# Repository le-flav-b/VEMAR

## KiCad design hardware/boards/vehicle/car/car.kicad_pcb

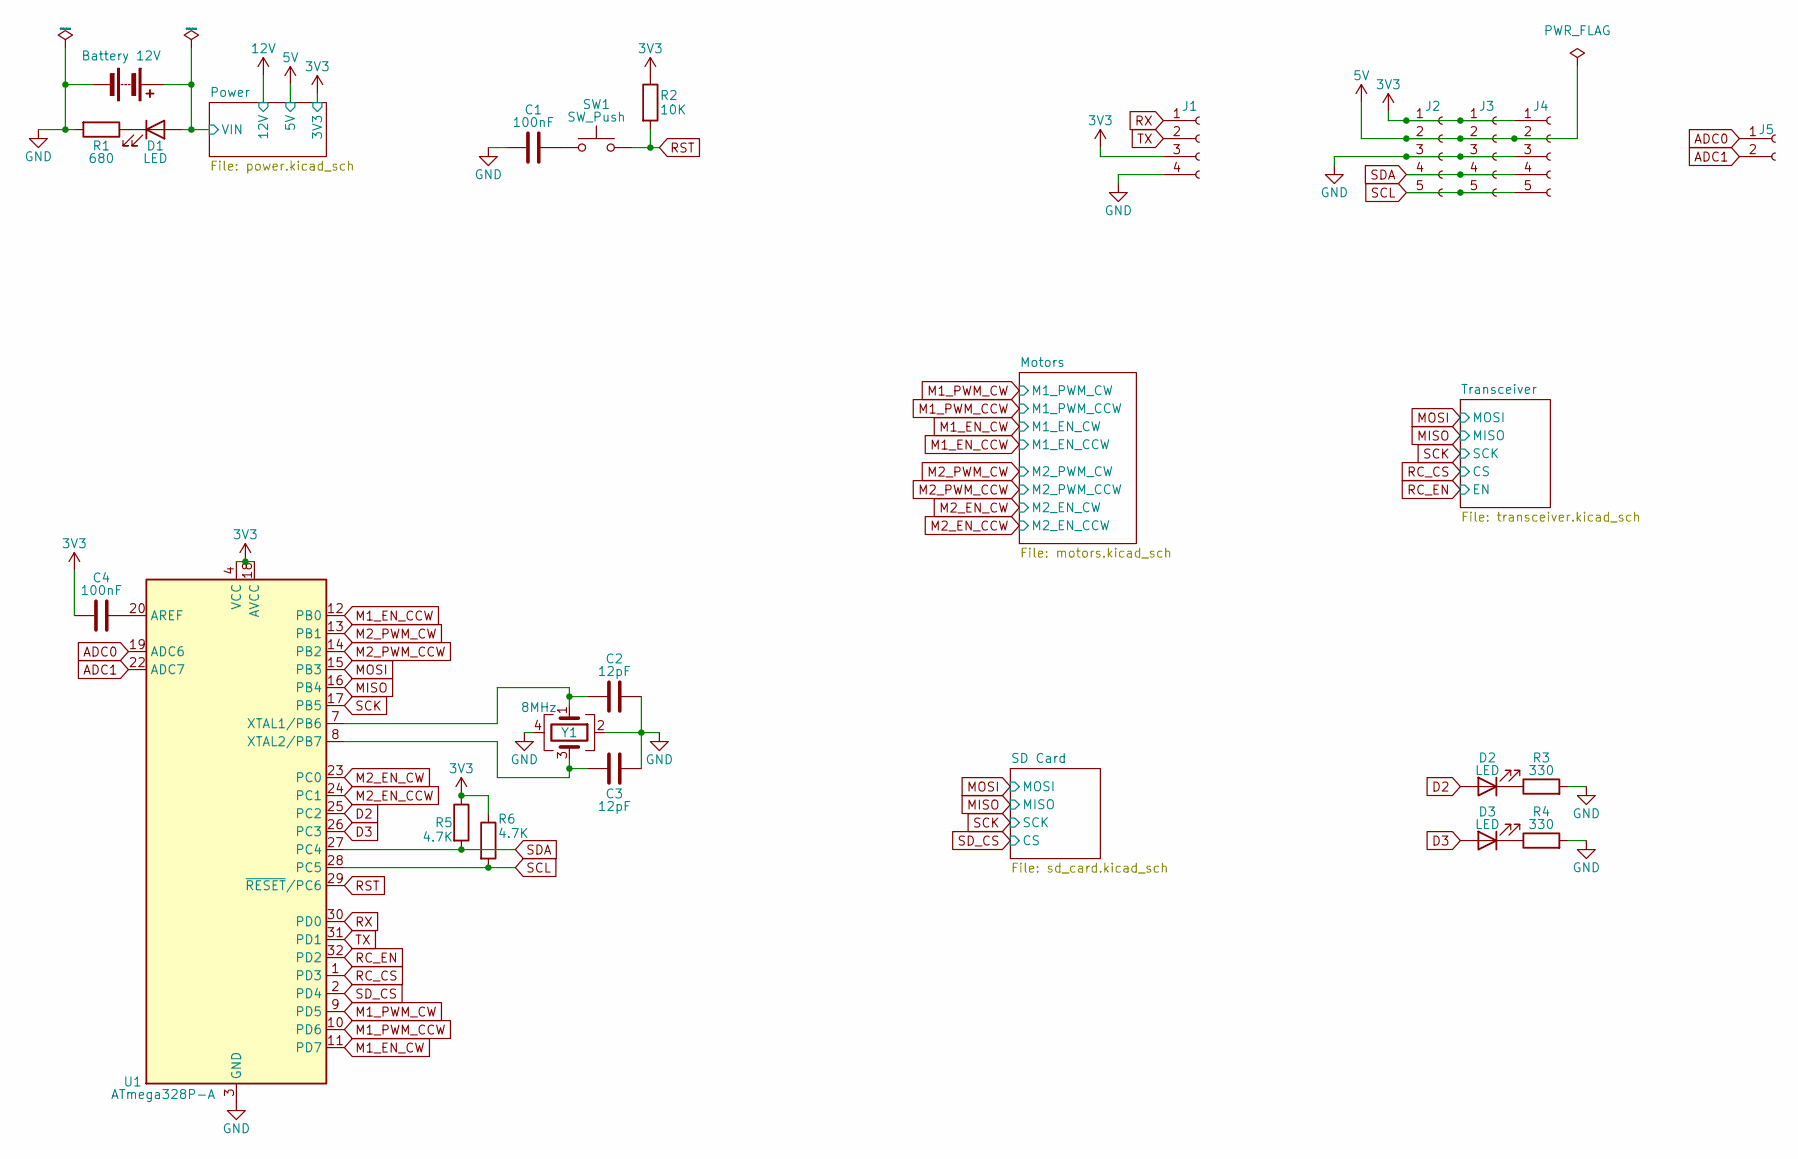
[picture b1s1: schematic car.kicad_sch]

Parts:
BT1: Battery 12V; PinHeader_1x02_P2.54mm_Vertical
C1, C4: 100nF; C_0603_1608Metric_Pad1.08x0.95mm_HandSolder
C2, C3: 12pF; C_0603_1608Metric_Pad1.08x0.95mm_HandSolder
D1, D2, D3: LED; LED_0603_1608Metric_Pad1.05x0.95mm_HandSolder
J1: Conn_01x04_Socket; PinHeader_1x04_P2.54mm_Vertical
J2, J3, J4: Conn_01x05_Socket; PinHeader_1x05_P2.54mm_Vertical
J5: Conn_01x02_Socket; PinHeader_1x02_P2.54mm_Vertical
R1: 680; R_0603_1608Metric_Pad0.98x0.95mm_HandSolder
R2: 10K; R_0603_1608Metric_Pad0.98x0.95mm_HandSolder
R3, R4: 330; R_0603_1608Metric_Pad0.98x0.95mm_HandSolder
R5, R6: 4.7K; R_0603_1608Metric_Pad0.98x0.95mm_HandSolder
SW1: SW_Push; SW_Tactile3x2.5
U1: ATmega328P-A; TQFP-32_7x7mm_P0.8mm
Y1: 8MHz; crys_osc_smd3225_4

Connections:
3V3: C4.1, J1.3, J2.1, J3.1, J4.1, R2.1, R5.1, R6.1, U1.4 (VCC), U1.6 (VCC), U1.18 (AVCC); also elsewhere on the board
5V: J2.2, J3.2, J4.2; also elsewhere on the board
12V: BT1.1 (+), D1.2 (A); also elsewhere on the board
ADC0: J5.1, U1.19 (ADC6)
ADC1: J5.2, U1.22 (ADC7)
D2: D2.2 (A), U1.25 (PC2)
D3: D3.2 (A), U1.26 (PC3)
GND: BT1.2 (-), C1.1, C2.2, C3.2, J1.4, J2.3, J3.3, J4.3, R1.2, R3.2, R4.2, U1.3 (GND), U1.5 (GND), U1.21 (GND), Y1.2, Y1.4; also elsewhere on the board
M1_EN_CCW: U1.12 (PB0); also elsewhere on the board
M1_EN_CW: U1.11 (PD7); also elsewhere on the board
M1_PWM_CCW: U1.10 (PD6); also elsewhere on the board
M1_PWM_CW: U1.9 (PD5); also elsewhere on the board
M2_EN_CCW: U1.24 (PC1); also elsewhere on the board
M2_EN_CW: U1.23 (PC0); also elsewhere on the board
M2_PWM_CCW: U1.14 (PB2); also elsewhere on the board
M2_PWM_CW: U1.13 (PB1); also elsewhere on the board
MISO: U1.16 (PB4); also elsewhere on the board
MOSI: U1.15 (PB3); also elsewhere on the board
unnamed: C1.2, SW1.1
unnamed: D1.1 (K), R1.1
unnamed: D2.1 (K), R3.1
unnamed: D3.1 (K), R4.1
unnamed: C4.2, U1.20 (AREF)
unnamed: C2.1, U1.7 (XTAL1/PB6), Y1.1
unnamed: C3.1, U1.8 (XTAL2/PB7), Y1.3
RC_CS: U1.1 (PD3); also elsewhere on the board
RC_EN: U1.32 (PD2); also elsewhere on the board
RST: R2.2, SW1.2, U1.29 (~RESET/PC6)
RX: J1.1, U1.30 (PD0)
SCK: U1.17 (PB5); also elsewhere on the board
SCL: J2.5, J3.5, J4.5, R6.2, U1.28 (PC5)
SDA: J2.4, J3.4, J4.4, R5.2, U1.27 (PC4)
SD_CS: U1.2 (PD4); also elsewhere on the board
TX: J1.2, U1.31 (PD1)

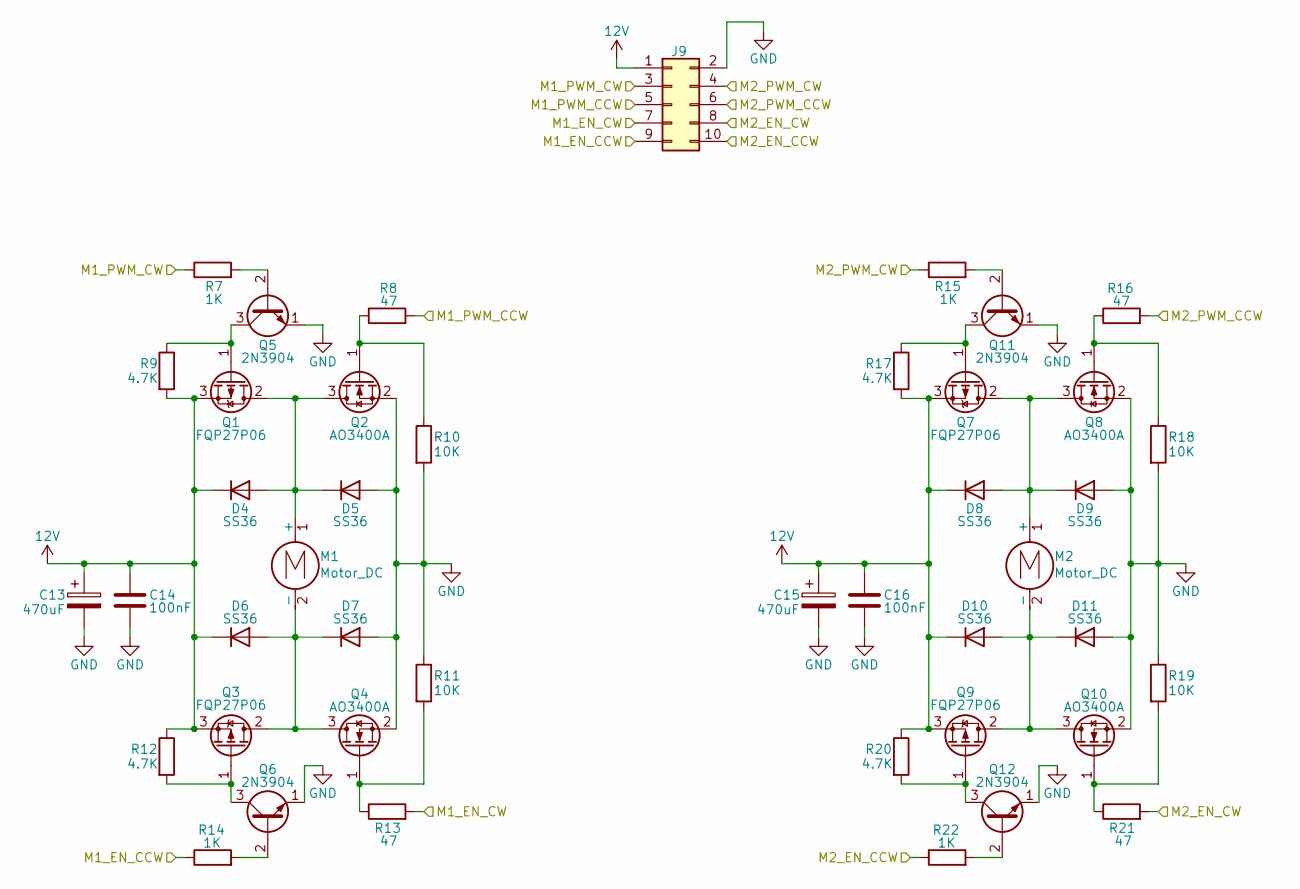
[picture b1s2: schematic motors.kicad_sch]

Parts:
C13, C15: 470uF; CP_Radial_D10.0mm_P5.00mm
C14, C16: 100nF; C_0603_1608Metric_Pad1.08x0.95mm_HandSolder
D4, D5, D6, D7, D8, D9, D10, D11: SS36; D_SMA_Handsoldering
J9: Conn_02x05_Odd_Even; PinHeader_2x05_P2.54mm_Vertical
M1, M2: Motor_DC; PinHeader_1x02_P2.54mm_Vertical
Q1, Q3, Q7, Q9: FQP27P06; TO-220-3_Vertical
Q2, Q4, Q8, Q10: AO3400A; SOT-23
Q5, Q6, Q11, Q12: 2N3904; TO-92_Inline
R7, R14, R15, R22: 1K; R_0603_1608Metric_Pad0.98x0.95mm_HandSolder
R8, R13, R16, R21: 47; R_0603_1608Metric_Pad0.98x0.95mm_HandSolder
R9, R12, R17, R20: 4.7K; R_0603_1608Metric_Pad0.98x0.95mm_HandSolder
R10, R11, R18, R19: 10K; R_0603_1608Metric_Pad0.98x0.95mm_HandSolder

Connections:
12V: C13.1, C14.1, C15.1, C16.1, D4.1 (K), D6.1 (K), D8.1 (K), D10.1 (K), J9.1, Q1.3 (S), Q3.3 (S), Q7.3 (S), Q9.3 (S), R9.2, R12.1, R17.2, R20.1; also elsewhere on the board
GND: C13.2, C14.2, C15.2, C16.2, D5.2 (A), D7.2 (A), D9.2 (A), D11.2 (A), J9.2, Q2.2 (S), Q4.2 (S), Q5.1 (E), Q6.1 (E), Q8.2 (S), Q10.2 (S), Q11.1 (E), Q12.1 (E), R10.2, R11.1, R18.2, R19.1; also elsewhere on the board
M1_EN_CCW: J9.9, R14.1; also elsewhere on the board
M1_EN_CW: J9.7, R13.2; also elsewhere on the board
M1_PWM_CCW: J9.5, R8.2; also elsewhere on the board
M1_PWM_CW: J9.3, R7.1; also elsewhere on the board
M2_EN_CCW: J9.10, R22.1; also elsewhere on the board
M2_EN_CW: J9.8, R21.2; also elsewhere on the board
M2_PWM_CCW: J9.6, R16.2; also elsewhere on the board
M2_PWM_CW: J9.4, R15.1; also elsewhere on the board
unnamed: D4.2 (A), D5.1 (K), M1.1 (+), Q1.2 (D), Q2.3 (D)
unnamed: D6.2 (A), D7.1 (K), M1.2 (-), Q3.2 (D), Q4.3 (D)
unnamed: D8.2 (A), D9.1 (K), M2.1 (+), Q7.2 (D), Q8.3 (D)
unnamed: D10.2 (A), D11.1 (K), M2.2 (-), Q9.2 (D), Q10.3 (D)
unnamed: Q1.1 (G), Q5.3 (C), R9.1
unnamed: Q2.1 (G), R8.1, R10.1
unnamed: Q3.1 (G), Q6.3 (C), R12.2
unnamed: Q4.1 (G), R11.2, R13.1
unnamed: Q5.2 (B), R7.2
unnamed: Q6.2 (B), R14.2
unnamed: Q8.1 (G), R16.1, R18.1
unnamed: Q10.1 (G), R19.2, R21.1
unnamed: Q11.2 (B), R15.2
unnamed: Q7.1 (G), Q11.3 (C), R17.1
unnamed: Q12.2 (B), R22.2
unnamed: Q9.1 (G), Q12.3 (C), R20.2

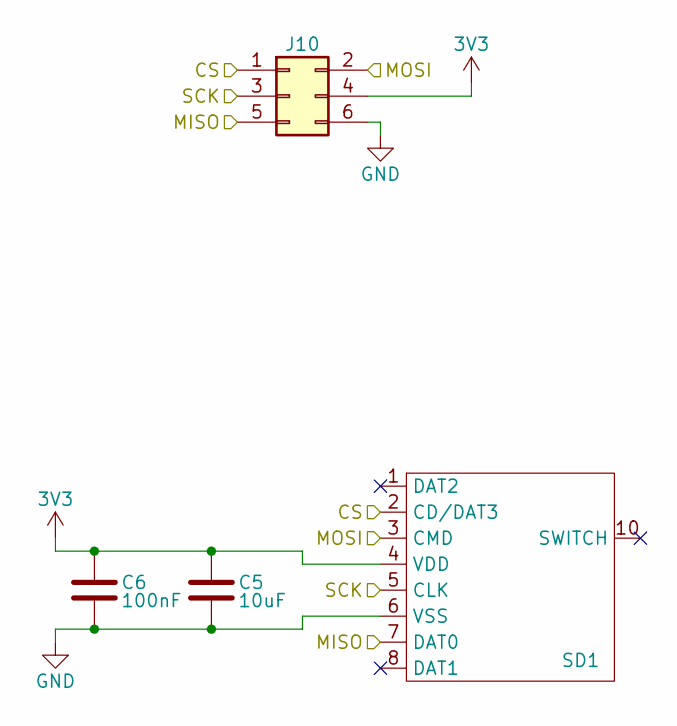
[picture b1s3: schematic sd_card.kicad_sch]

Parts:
C5: 10uF; C_0603_1608Metric_Pad1.08x0.95mm_HandSolder
C6: 100nF; C_0603_1608Metric_Pad1.08x0.95mm_HandSolder
J10: Conn_02x03_Odd_Even; PinHeader_2x03_P2.54mm_Vertical
SD1: SD_SLOT

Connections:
3V3: C5.1, C6.1, J10.4, SD1.4 (VDD); also elsewhere on the board
GND: C5.2, C6.2, J10.6, SD1.6 (VSS); also elsewhere on the board
MISO: J10.5, SD1.7 (DAT0); also elsewhere on the board
MOSI: J10.2, SD1.3 (CMD); also elsewhere on the board
SCK: J10.3, SD1.5 (CLK); also elsewhere on the board
SD_CS: J10.1, SD1.2 (CD/DAT3); also elsewhere on the board

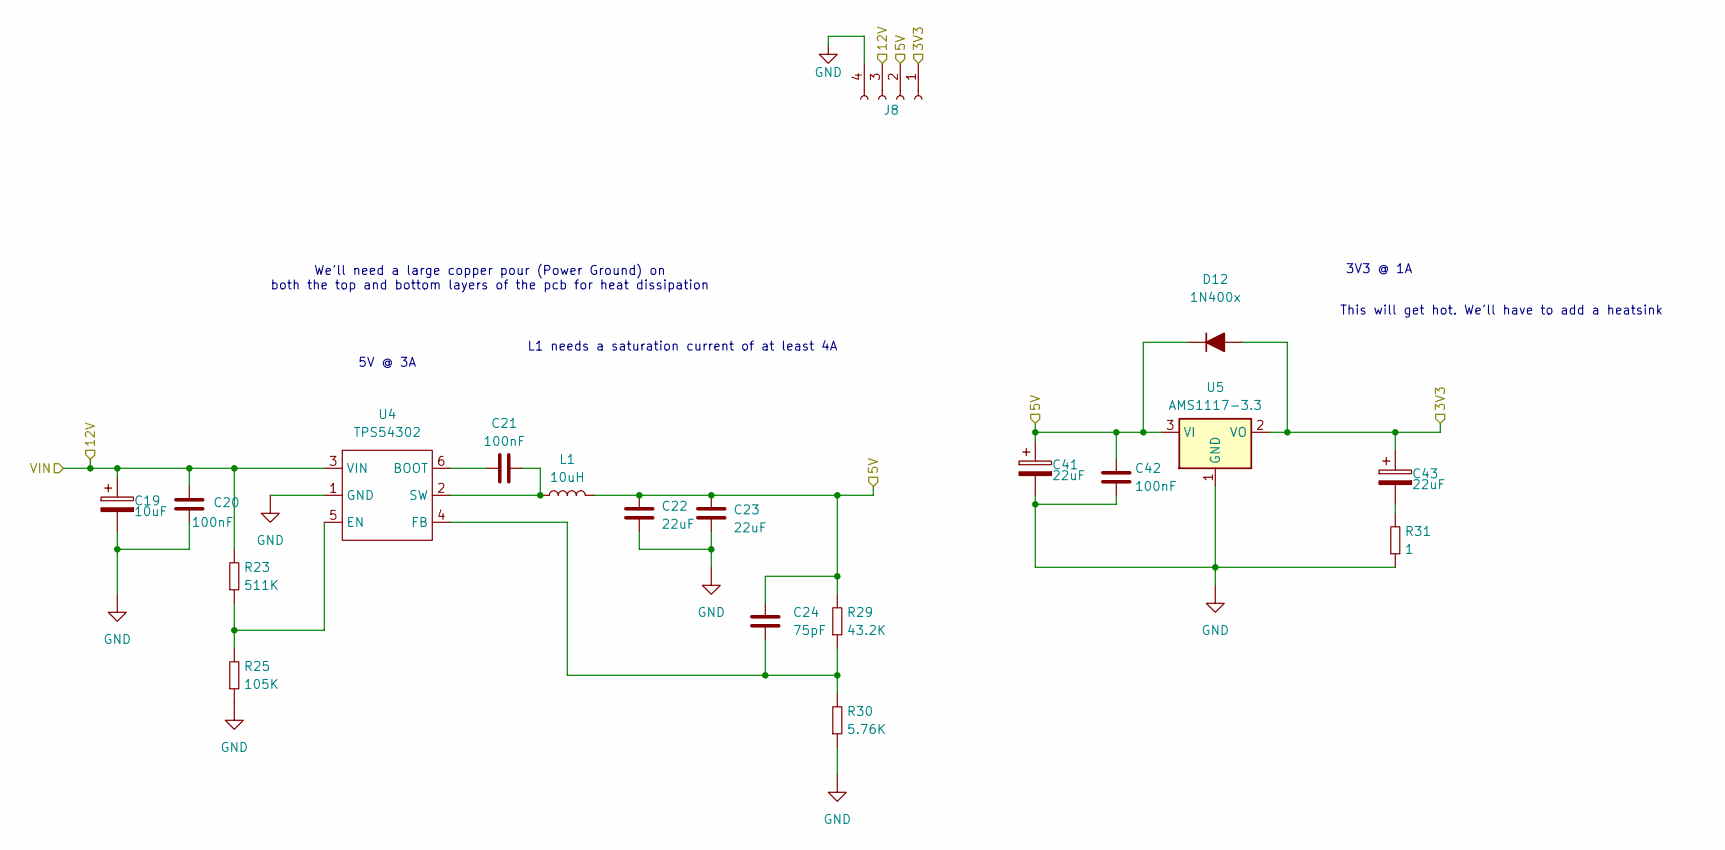
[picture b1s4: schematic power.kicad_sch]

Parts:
C19: 10uF; CP_Radial_D5.0mm_P2.00mm
C20, C21, C42: 100nF; C_0603_1608Metric_Pad1.08x0.95mm_HandSolder
C22, C23: 22uF; C_0603_1608Metric_Pad1.08x0.95mm_HandSolder
C24: 75pF; C_0603_1608Metric_Pad1.08x0.95mm_HandSolder
C41, C43: 22uF; CP_Radial_D5.0mm_P2.00mm
D12: 1N400x; D_DO-41_SOD81_P2.54mm_Vertical_AnodeUp
J8: Conn_01x04_Socket; PinHeader_1x04_P2.54mm_Vertical
L1: 10uH; L_0603_1608Metric_Pad1.05x0.95mm_HandSolder
R23: 511K; R_0603_1608Metric_Pad0.98x0.95mm_HandSolder
R25: 105K; R_0603_1608Metric_Pad0.98x0.95mm_HandSolder
R29: 43.2K; R_0603_1608Metric_Pad0.98x0.95mm_HandSolder
R30: 5.76K; R_0603_1608Metric_Pad0.98x0.95mm_HandSolder
R31: 1; R_0603_1608Metric_Pad0.98x0.95mm_HandSolder
U4: TPS54302; TSOT-23-6_HandSoldering
U5: AMS1117-3.3; SOT-223-3_TabPin2

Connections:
3V3: C43.1, D12.2 (A), J8.1, U5.2 (VO); also elsewhere on the board
5V: C22.1, C23.2, C24.2, C41.1, C42.2, D12.1 (K), J8.2, L1.2, R29.2, U5.3 (VI); also elsewhere on the board
12V: C19.1, C20.2, J8.3, R23.2, U4.3 (VIN); also elsewhere on the board
GND: C19.2, C20.1, C22.2, C23.1, C41.2, C42.1, J8.4, R25.1, R30.1, R31.1, U4.1 (GND), U5.1 (GND); also elsewhere on the board
unnamed: C43.2, R31.2
unnamed: C21.1, U4.6 (BOOT)
unnamed: R23.1, R25.2, U4.5 (EN)
unnamed: C24.1, R29.1, R30.2, U4.4 (FB)
unnamed: C21.2, L1.1, U4.2 (SW)

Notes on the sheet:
We'll need a large copper pour (Power Ground) on both the top and bottom layers of the pcb for heat dissipation
5V @ 3A
L1 needs a saturation current of at least 4A
This will get hot. We'll have to add a heatsink
3V3 @ 1A

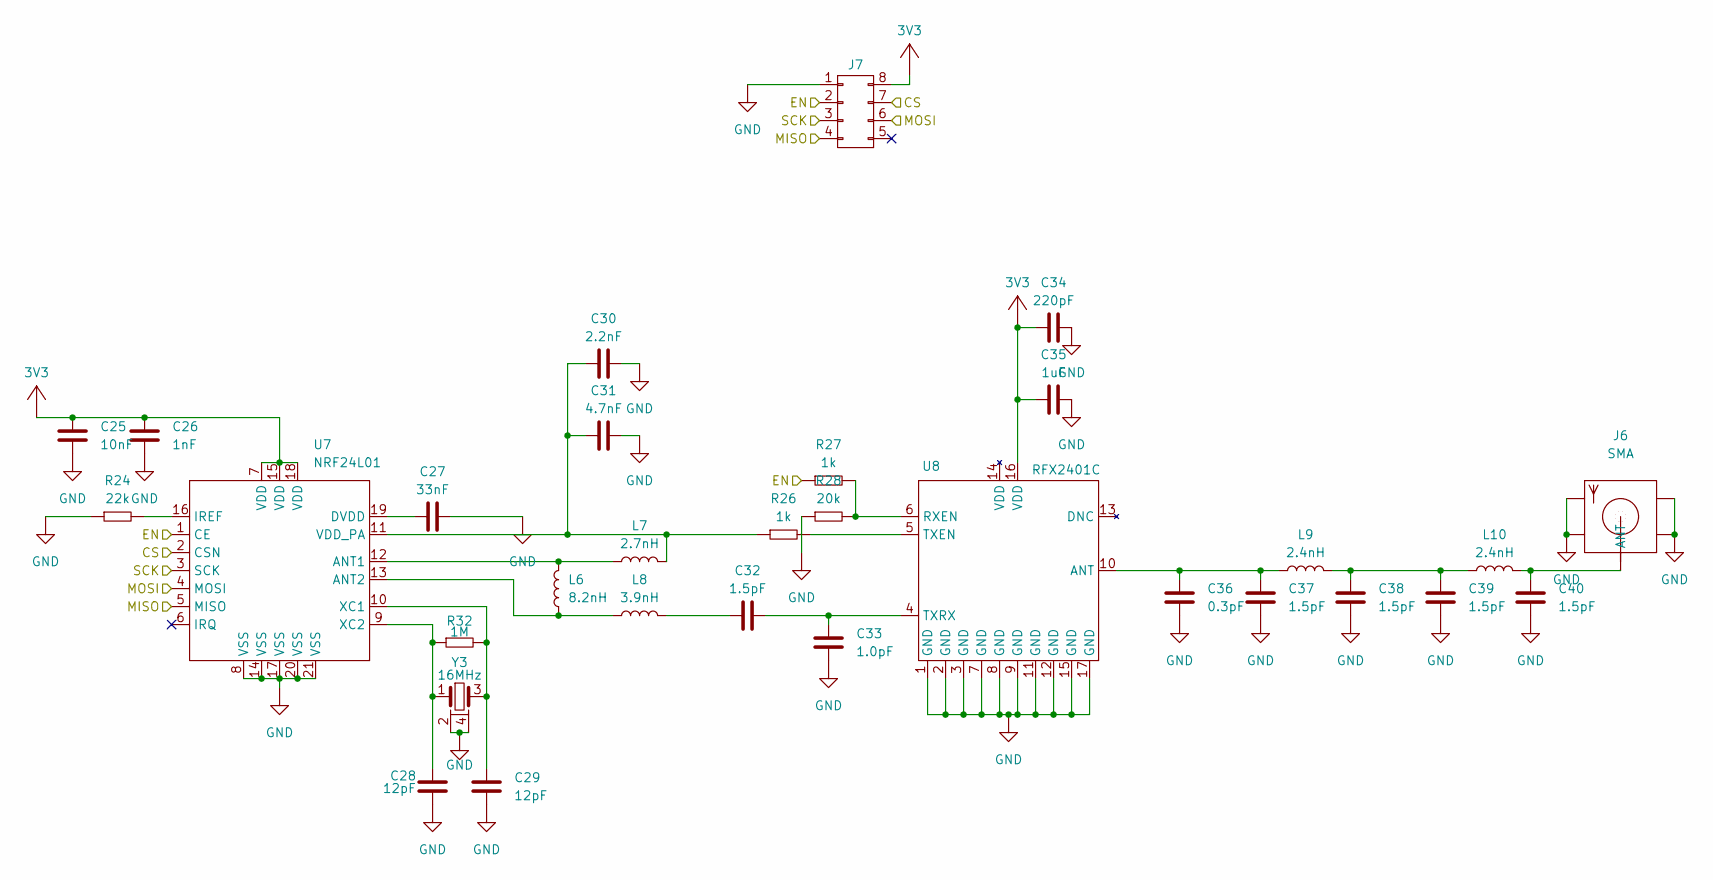
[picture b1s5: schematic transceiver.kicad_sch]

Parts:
C25: 10nF; C_0603
C26: 1nF; C_0603
C27: 33nF; C_0603
C28, C29: 12pF; C_0603
C30: 2.2nF; C_0603
C31: 4.7nF; C_0603
C32, C37, C38, C39, C40: 1.5pF; C_0603
C33: 1.0pF; C_0603
C34: 220pF; C_0603
C35: 1uF; C_0603
C36: 0.3pF; C_0603
J6: SMA
J7: 02x04; Pin_02x04
L6: 8.2nH; L_0603
L7: 2.7nH; L_0603
L8: 3.9nH; L_0603
L9, L10: 2.4nH; L_0603
R24: 22k; R_0603
R26, R27: 1k; R_0603
R28: 20k; R_0603
R32: 1M; R_0603
U7: NRF24L01; NRF24L01_QFN20
U8: RFX2401C; RFX2401C_QFN16
Y3: 16MHz; Crystal_3225

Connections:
3V3: C25.2, C26.2, C34.1, C35.1, J7.8, U7.7 (VDD), U7.15 (VDD), U7.18 (VDD), U8.16 (VDD); also elsewhere on the board
GND: C25.1, C26.1, C27.2, C28.1, C29.1, C30.2, C31.2, C33.1, C34.2, C35.2, C36.1, C37.1, C38.1, C39.1, C40.1, J6.2, J6.3, J6.4, J6.5, J7.1, R24.1, R28.1, U7.8 (VSS), U7.14 (VSS), U7.17 (VSS), U7.20 (VSS), U7.21 (VSS), U8.1 (GND), U8.2 (GND), U8.3 (GND), U8.7 (GND), U8.8 (GND), U8.9 (GND), U8.11 (GND), U8.12 (GND), U8.15 (GND), U8.17 (GND), Y3.2 (GND), Y3.4 (GND); also elsewhere on the board
MISO: J7.4, U7.5 (MISO); also elsewhere on the board
MOSI: J7.6, U7.4 (MOSI); also elsewhere on the board
unnamed: C32.1, L8.2
unnamed: C38.2, C39.2, L9.2, L10.1
unnamed: C40.2, J6.1 (ANT), L10.2
unnamed: L6.2, L7.1, U7.12 (ANT1)
unnamed: L6.1, L8.1, U7.13 (ANT2)
unnamed: C27.1, U7.19 (DVDD)
unnamed: R24.2, U7.16 (IREF)
unnamed: C30.1, C31.1, L7.2, R26.1, U7.11 (VDD_PA)
unnamed: C29.2, R32.2, U7.10 (XC1), Y3.3
unnamed: C28.2, R32.1, U7.9 (XC2), Y3.1
unnamed: C36.2, C37.2, L9.1, U8.10 (ANT)
unnamed: R27.2, R28.2, U8.6 (RXEN)
unnamed: R26.2, U8.5 (TXEN)
unnamed: C32.2, C33.2, U8.4 (TXRX)
RC_CS: J7.7, U7.2 (CSN); also elsewhere on the board
RC_EN: J7.2, R27.1, U7.1 (CE); also elsewhere on the board
SCK: J7.3, U7.3 (SCK); also elsewhere on the board

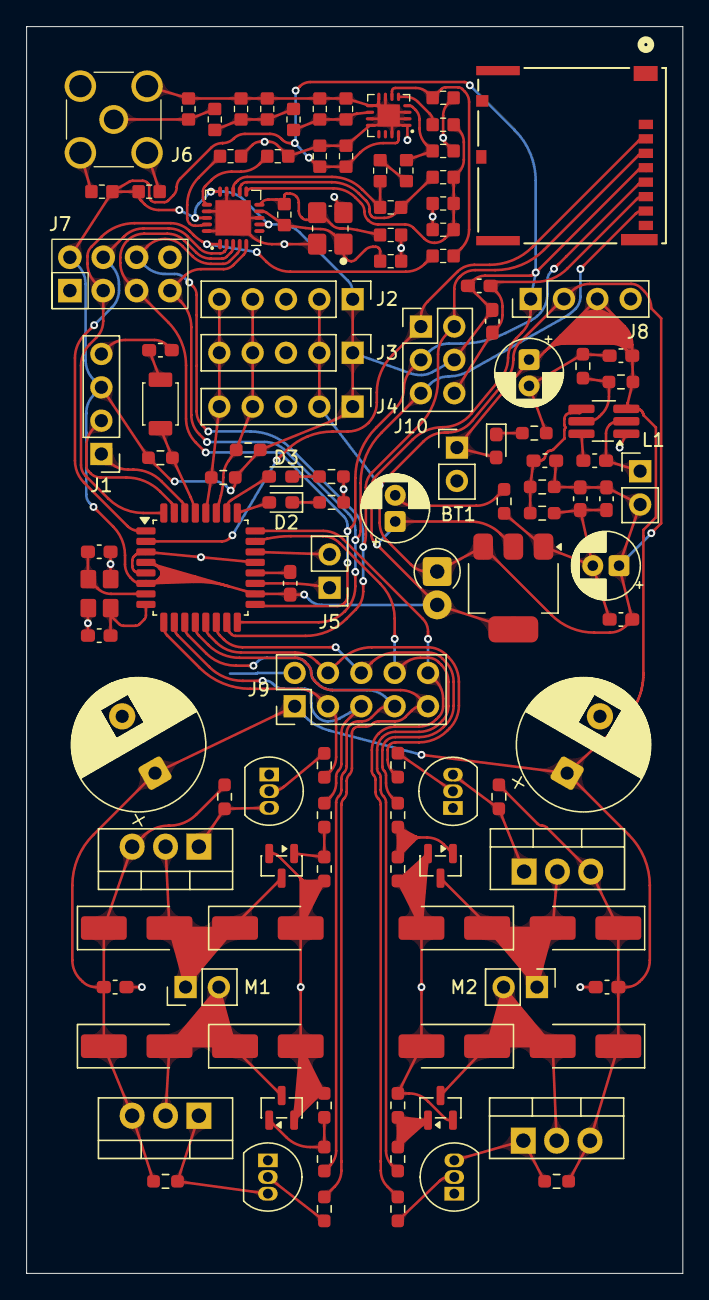
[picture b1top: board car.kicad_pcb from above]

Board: 2 copper layers, 50.0 x 95.0 mm, 119 parts (0 on the bottom side), 69 nets.

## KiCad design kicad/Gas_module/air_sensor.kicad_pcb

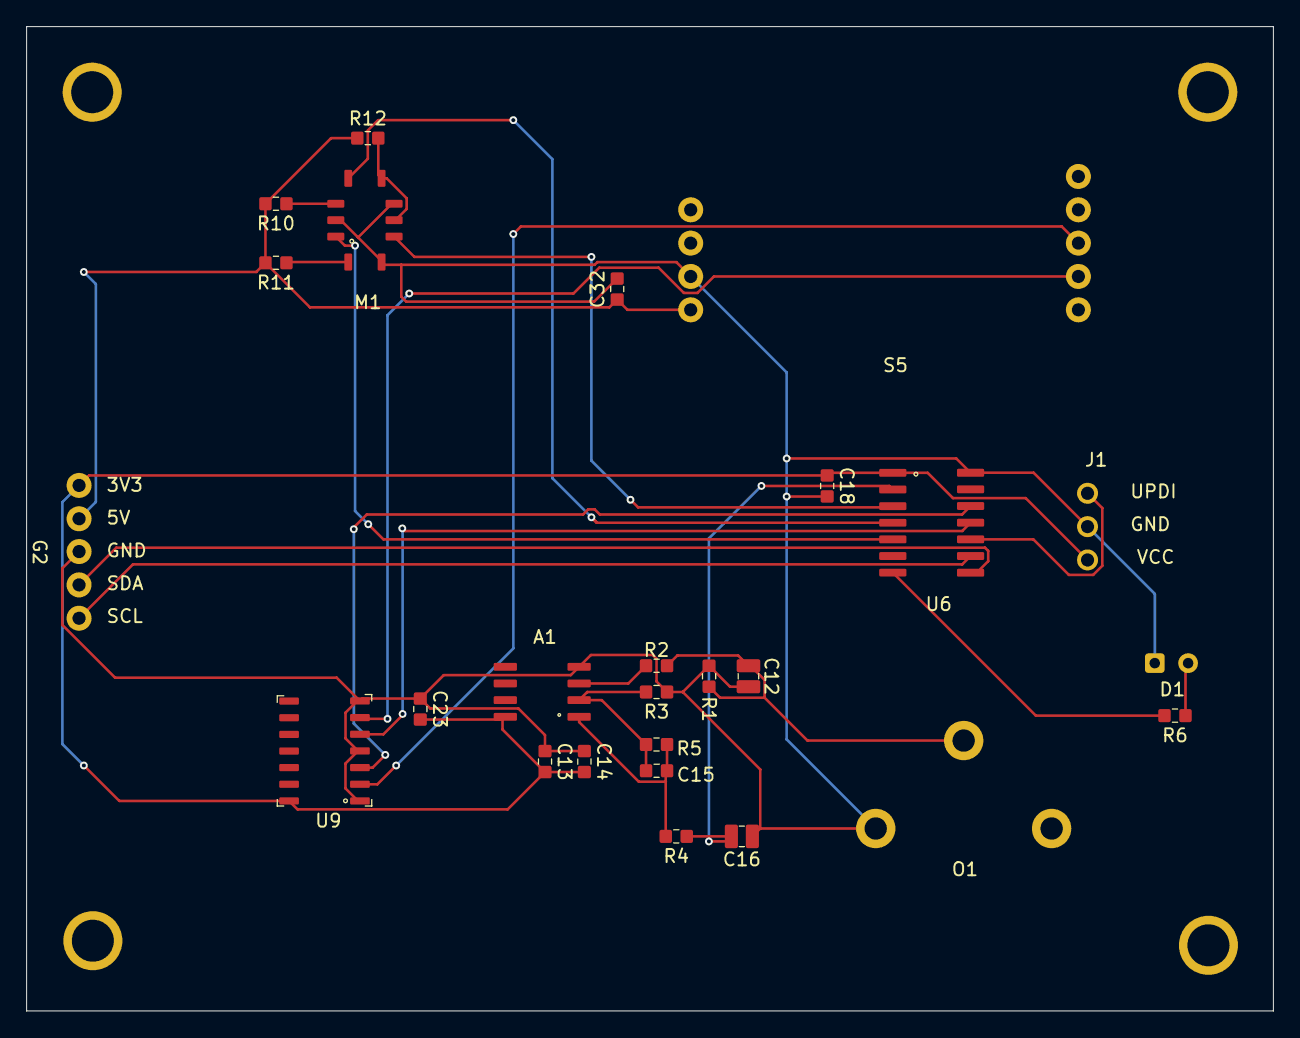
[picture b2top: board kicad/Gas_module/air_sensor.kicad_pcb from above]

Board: 2 copper layers, 95.0 x 75.0 mm, 26 parts (0 on the bottom side), 23 nets.

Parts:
A1: AD8552
C12: 4.7uF; C_0805
C13, C14, C15: 10nF; C_0603
C16: 10uF; C_0805
C18, C23, C32: 100nF; C_0603
D1: LED_3mm_THT
G2: Module Connector; GPIO_HEADER
J1: Program Header; ATtiny_Programming_Header
M1: MiCS-6814
O1: AO-03; AO_03
R1, R4: 100R; R_0603
R2, R3: 10K; R_0603
R5: 400K; R_0603
R6: 220; R_0603
R10: 27R; R_0603
R11: 130; R_0603
R12: 820R; R_0603
S5: MH-Z1911A
U6: ATtiny1614
U9: Buffer; SN74LVC125

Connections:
02_A: C16.2, R4.1, U6.2 (PA4)
3V3: A1.8 (+Vs), C13.2, C14.2, C18.1, C23.2, G2.1 (3V3), J1.1 (VCC), U6.1 (VDD), U9.14 (VCC)
5V: C32.1, G2.2 (5V), R10.2, R11.2, R12.1, S5.9 (VIN)
AT_GAS_RX: U6.12 (PA2), U9.3 (1Y)
AT_GAS_TX: U6.11 (PA1), U9.5 (2A)
C02_RX: S5.4 (RX), U9.6 (2Y)
CO2_TX: S5.3 (TX), U9.2 (1A)
CO_VAL: M1.8 (H), U6.3 (PA5)
GND: A1.4 (-Vs), C12.2, C13.1, C14.1, C16.1, C18.2, C23.1, C32.2, D1.1 (K), G2.3 (GND), J1.2 (GND), M1.2 (B), M1.6 (F), M1.9 (J), O1.2 (Vsensor-), R1.1, R3.1, S5.8 (GND), U6.14 (GND), U9.1 (1OE), U9.4 (2OE), U9.7 (GND)
NH3_VAL: M1.4 (D), U6.4 (PA6)
NO2_VAL: M1.1 (A), U6.5 (PA7)
unnamed: A1.3 (+IN_A), R2.2
unnamed: A1.2 (-IN_A), C15.2, R3.2, R5.2
unnamed: A1.1 (OUT_A), C15.1, R4.2, R5.1
unnamed: D1.2 (A), R6.2
unnamed: M1.3 (C), R10.1
unnamed: M1.5 (E), M1.7 (G), R12.2
unnamed: M1.10 (K), R11.1
unnamed: C12.1, O1.1 (Vsensor+), R1.2, R2.1
SCL: G2.5 (SCL), U6.9 (PB0)
SDA: G2.4 (SDA), U6.8 (PB1)
STATUS_LED: R6.1, U6.7 (TOSC2/PB2)
UPDI: J1.3 (UPDI), U6.10 (PA0/RST/UPDI)

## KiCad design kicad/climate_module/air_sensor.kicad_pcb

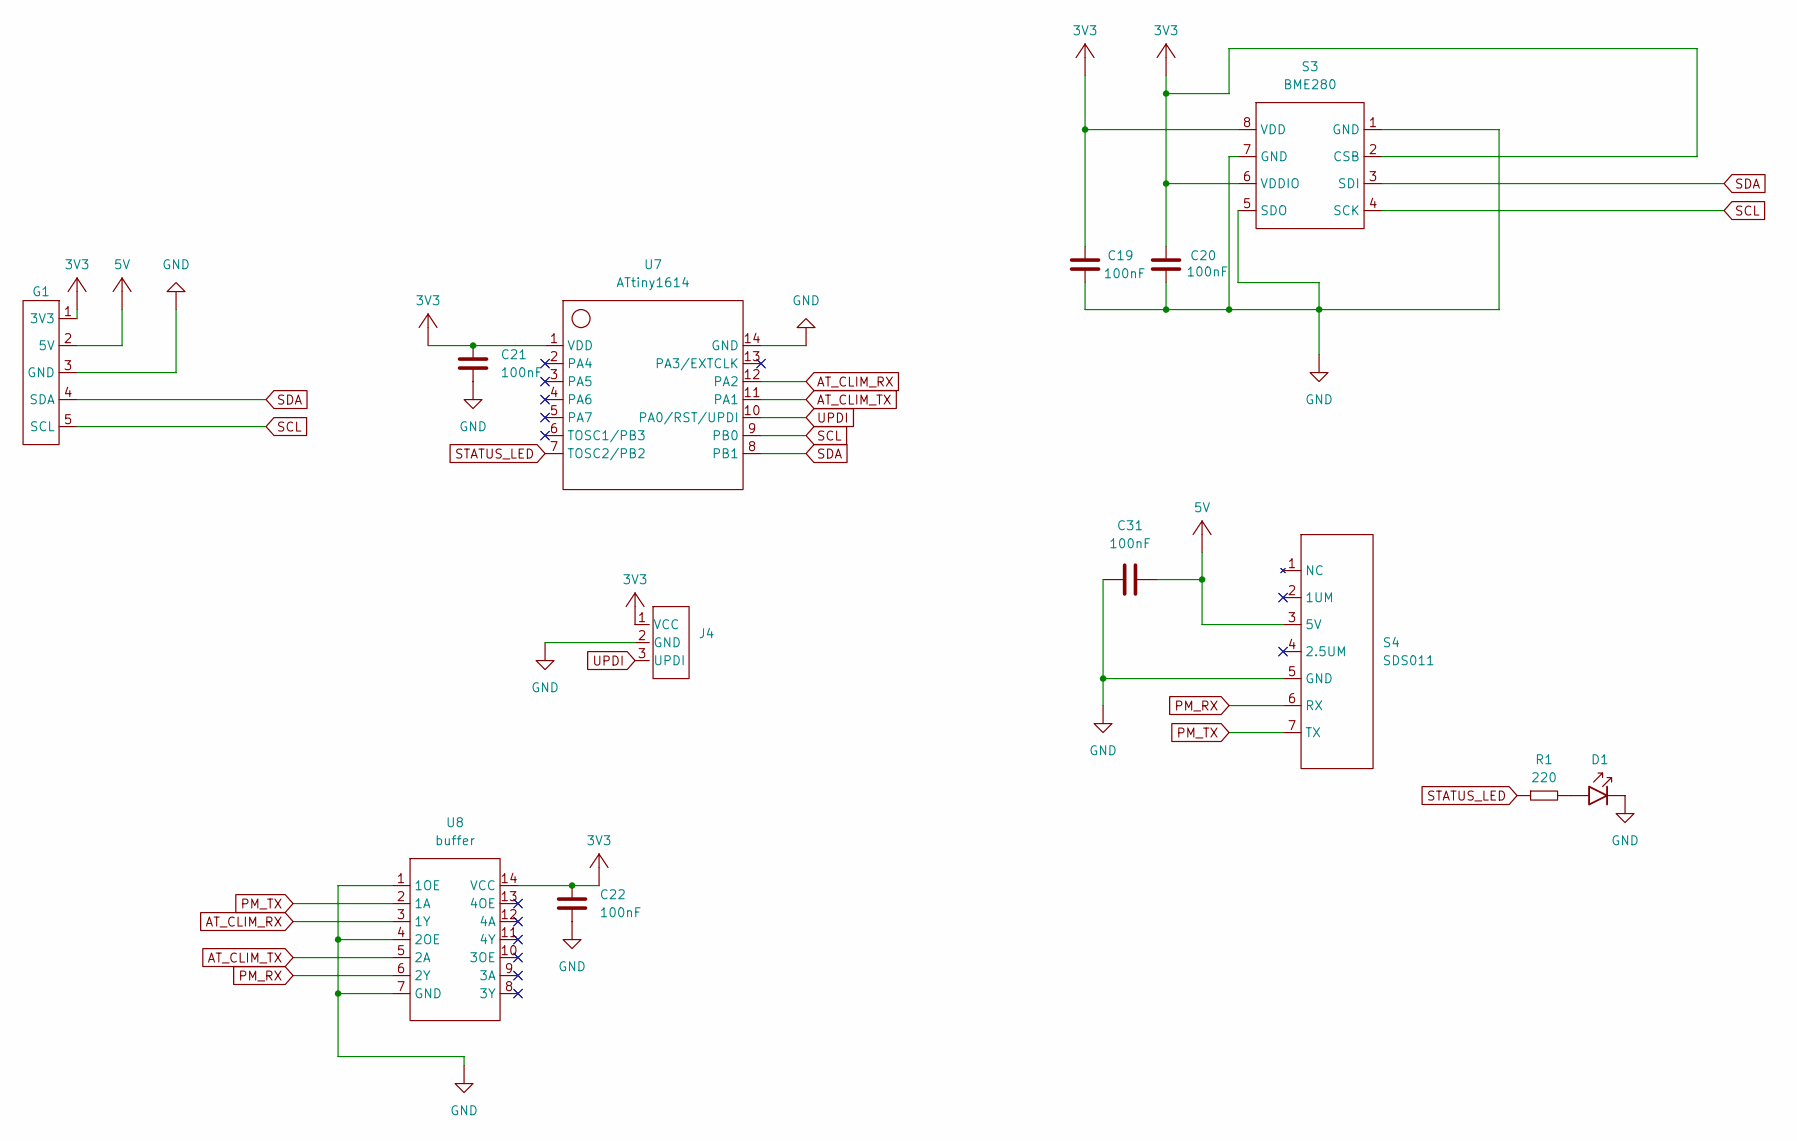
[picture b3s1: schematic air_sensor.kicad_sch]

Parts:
C19, C20, C21, C22, C31: 100nF; C_0603
D1: LED_3mm_THT
G1: GPIO_HEADER
J4: ATtiny_Programming_Header
R1: 220; R_0603
S3: BME280
S4: SDS011
U7: ATtiny1614
U8: buffer; SN74LVC125

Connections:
3V3: C19.1, C20.2, C21.2, C22.2, G1.1 (3V3), J4.1 (VCC), S3.2 (CSB), S3.6 (VDDIO), S3.8 (VDD), U7.1 (VDD), U8.14 (VCC)
5V: C31.2, G1.2 (5V), S4.3 (5V)
AT_CLIM_RX: U7.12 (PA2), U8.3 (1Y)
AT_CLIM_TX: U7.11 (PA1), U8.5 (2A)
GND: C19.2, C20.1, C21.1, C22.1, C31.1, D1.1 (K), G1.3 (GND), J4.2 (GND), S3.1 (GND), S3.5 (SDO), S3.7 (GND), S4.5 (GND), U7.14 (GND), U8.1 (1OE), U8.4 (2OE), U8.7 (GND)
unnamed: D1.2 (A), R1.2
PM_RX: S4.6 (RX), U8.6 (2Y)
PM_TX: S4.7 (TX), U8.2 (1A)
SCL: G1.5 (SCL), S3.4 (SCK), U7.9 (PB0)
SDA: G1.4 (SDA), S3.3 (SDI), U7.8 (PB1)
STATUS_LED: R1.1, U7.7 (TOSC2/PB2)
UPDI: J4.3 (UPDI), U7.10 (PA0/RST/UPDI)

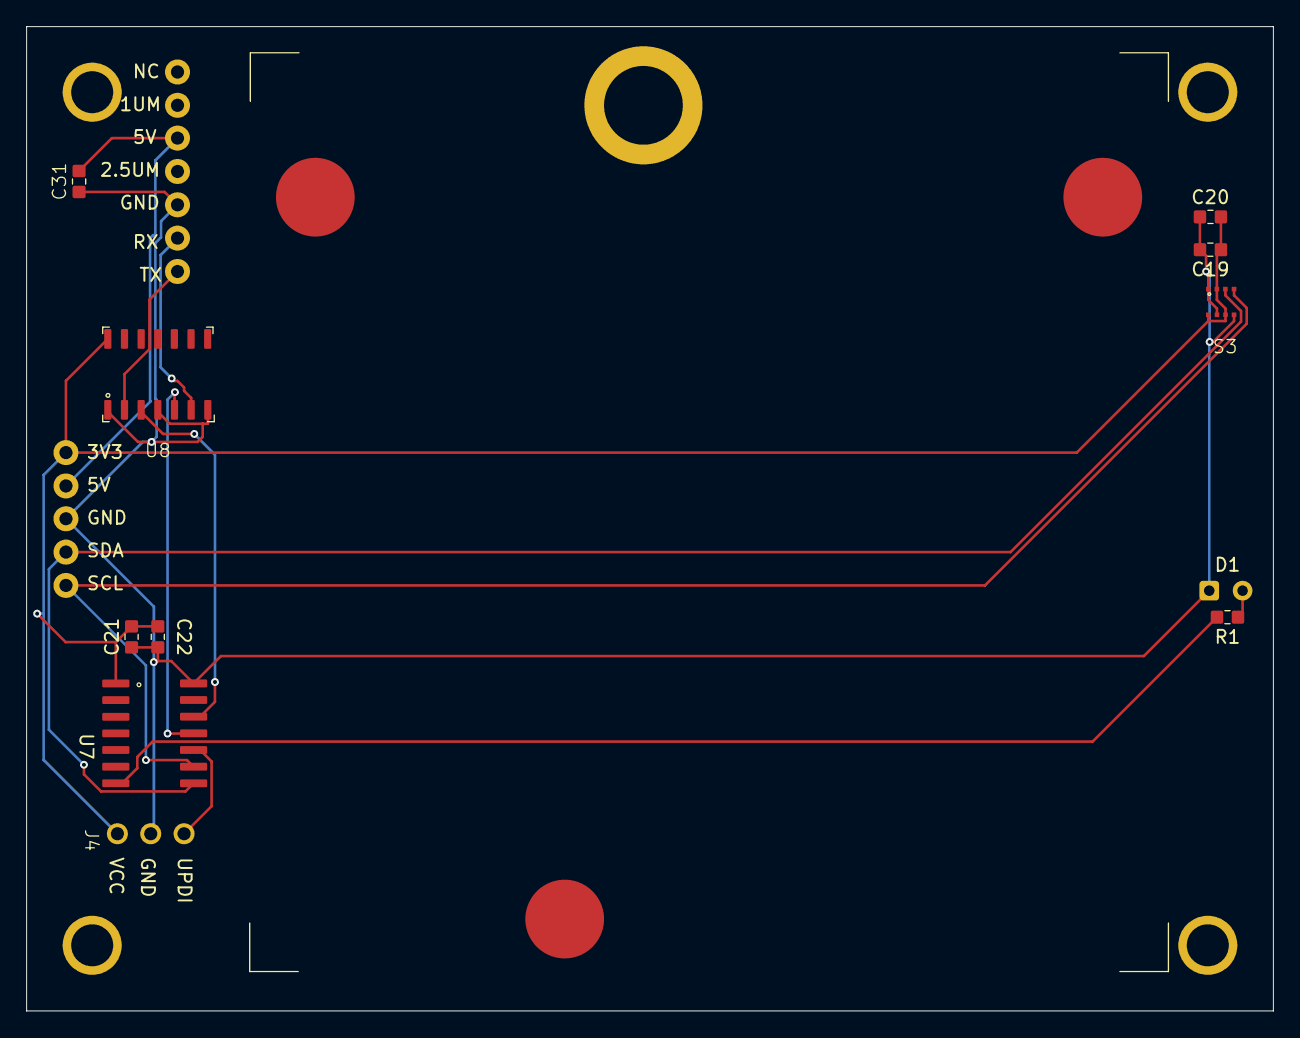
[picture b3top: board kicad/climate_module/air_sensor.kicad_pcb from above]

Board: 2 copper layers, 95.0 x 75.0 mm, 13 parts (0 on the bottom side), 12 nets.
